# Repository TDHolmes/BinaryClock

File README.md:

# Binary Clock
A simple clock that displays the time in [binary coded decimal][BCD wiki link].

## PCB

![alt text][PCB picture]

The current design uses an Atmel [ATtiny4313][attiny link] microcontroller in conjunction with a Maxim [DS3231M][ds3231m link] [RTC][RTC wiki link] for accurate time keeping. The LEDs are driven with a [STP16CPC26][stp16cpc26 link] constant current LED driver along with [high-side MOSFETs][mosfet wiki link] for [multiplexing][multiplexing wiki link].

## LED Driving Scheme

The LEDs are driven by multiplexing the rows and columns. The columns are dirven individually via PMOS transistors. The rows are daisy chained and driven by the [STP16CPC26][stp16cpc26 link]. The columns are refreshed at an effective rate of 360 Hz to be equivallent to 60 Hz refresh rate.

In order to get more than basic red, green and blue combinations, the LEDs have four time slots to create more color combinations. So in reality, the LEDs are updated at (60 Hz) * (6 columns) * (4 bit color) = 1440 Hz.

Below shows the connectivity of the LEDs to the driver chips.

![alt text][Multiplex - off]

Below is a snapshot in time when the minute ones column is active.

![alt text][Multiplex - on]

And below is a gif of multiplexing in action.

![alt text][GIF]

## GUI
The user interface communicates to the PCB via a [UART][UART wiki link] through a USB to serial converter chip. The user interface can do a few things:
- set the time to the current computer system time
- set a custom time
- set one or all LEDs to a certain color
- clear one or all LEDs

![alt text][GUI picture]

[BCD wiki link]: https://en.wikipedia.org/wiki/Binary-coded_decimal
[attiny link]: https://www.atmel.com/devices/ATTINY4313.aspx
[ds3231m link]: https://www.maximintegrated.com/en/products/digital/real-time-clocks/DS3231M.html
[stp16cpc26 link]: https://www.st.com/content/st_com/en/products/power-management/led-drivers/led-array-drivers/stp16cpc26.html
[Multiplex - off]: https://raw.githubusercontent.com/TDHolmes/BinaryClock/master/documents/pictures/binaryClock_multiplexLogic_notOn.png "Diagram of the connections if the LEDs"
[Multiplex - on]: https://raw.githubusercontent.com/TDHolmes/BinaryClock/master/documents/pictures/binaryClock_multiplexLogic_on.png "Diagram of a snapshot when the minute ones column is active."
[GIF]: https://raw.githubusercontent.com/TDHolmes/BinaryClock/master/documents/pictures/binary_clock_demo.gif "GIF of the multiplexing"
[PCB picture]: https://raw.githubusercontent.com/TDHolmes/BinaryClock/master/documents/pictures/BinaryClock_rev1.JPG "Binary Clock v1 displaying 20:31:08 (8:31 PM)"
[RTC wiki link]: https://en.wikipedia.org/wiki/Real-time_clock
[mosfet wiki link]: https://en.wikipedia.org/wiki/MOSFET#Single-type
[multiplexing wiki link]: https://en.wikipedia.org/wiki/Multiplexing
[GUI picture]: https://raw.githubusercontent.com/TDHolmes/BinaryClock/master/documents/pictures/BinaryClockGUI.png "Binary Clock GUI v1.0"
[UART wiki link]: https://en.wikipedia.org/wiki/Universal_asynchronous_receiver/transmitter

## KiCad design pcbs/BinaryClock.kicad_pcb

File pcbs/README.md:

# Binary-Clock-v2.0
Board and schematic for the binary clock project.

<br />This work is licensed under a <a rel="license" href="http://creativecommons.org/licenses/by-nc-sa/4.0/">Creative Commons Attribution-NonCommercial-ShareAlike 4.0 International License</a>.

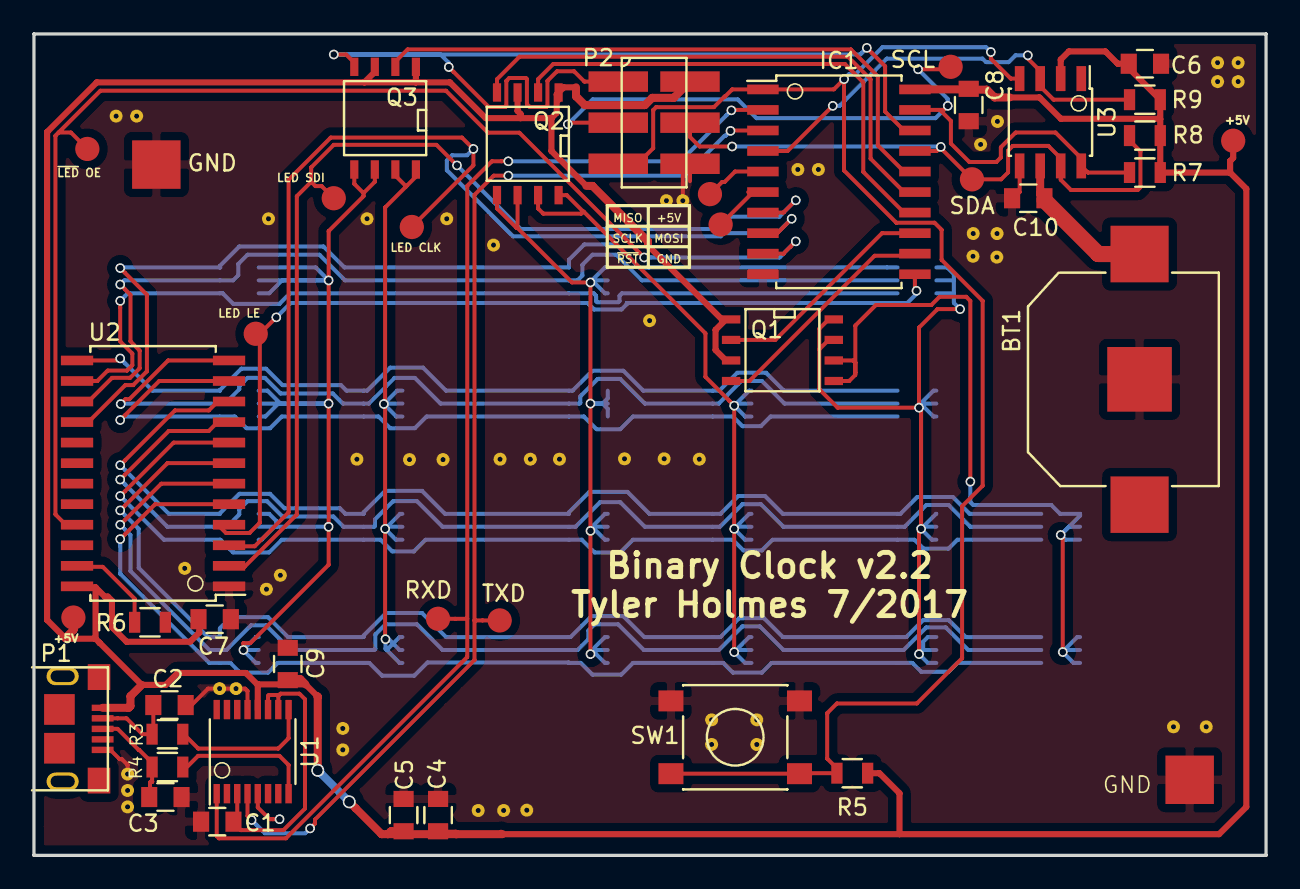
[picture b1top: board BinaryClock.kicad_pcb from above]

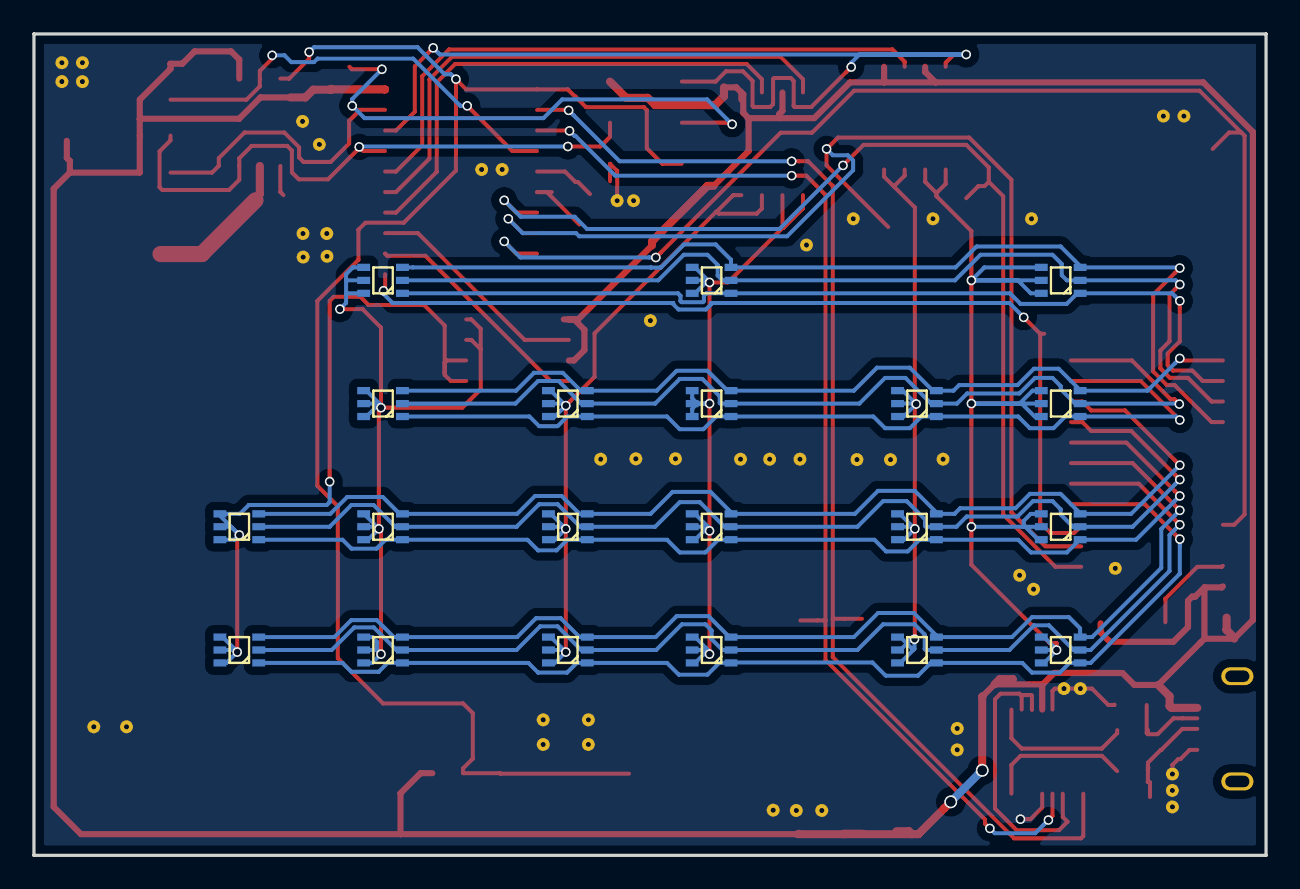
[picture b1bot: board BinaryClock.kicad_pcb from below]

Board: 2 copper layers, 76.2 x 50.8 mm, 62 parts (20 on the bottom side), 45 nets.

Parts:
BT1: CR1220; S8201-46R
C1: .1 uF; C_0805
C2, C3: 47 pF; C_0805
C4: 1 uF; C_0805
C5: 4.7 uF; C_0805
C6, C7, C8, C9, C10: 0.1 uF; C_0805
D_H_1, D_H_2, D_H_4, D_H_8, D_H_10, D_H_20: CLY6D-FKC; CREELED_6
D_M_1, D_M_2, D_M_4, D_M_8, D_M_10, D_M_20, D_M_40: CLY6D-FKC; CREELED_6
D_S_1, D_S_2, D_S_4, D_S_8, D_S_10, D_S_20, D_S_40: CLY6D-FKC; CREELED_6
IC1: ATTINY2313A-S; SOIC-20_7.5x12.8mm_Pitch1.27mm
P1: USB_OTG; 2013499-1
P2: CONN_02X03; 2x3_header_smd_0.1in
Q1, Q2, Q3: DMG9933USD; SOIC-8-N
R3, R4: R27; R_0805
R5, R7, R8, R9: 1K; R_0805
R6: 2K; R_0805
SW1: SW_PUSH; SW_SPST_PTS645
U1: FT230XS; SSOP-16_3.9x4.9mm_Pitch0.635mm
U2: STP16CPC26; SOIC-24_7.5x15.4mm_Pitch1.27mm
U3: DS3231M; SOIC-8_3.9x4.9mm_Pitch1.27mm
W1, W2, W5, W6, W7, W8, W9, W10, W11, W12, W13, W14: TEST_1P; Measurement_Point_Round-SMD-Pad_Small
W3, W4: TEST_1P; Measurement_Point_Square-SMD-Pad_Big

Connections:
+5V: C4.1, C5.1, C6.1, C7.1, C8.1, C9.1, IC1.20, P1.1, P2.2, Q1.1, Q1.3, Q2.1, Q2.3, Q3.1, Q3.3, R5.1, R7.1, R8.1, R9.1, U1.12, U2.24, U3.2, W1.1, W2.1
+BATT: BT1.1, C10.1, U3.6
/LED_Sheet/BLU_EIG_CAT: D_H_8.1, D_M_8.1, D_S_8.1, U2.14
/LED_Sheet/BLU_FOU_CAT: D_H_4.1, D_M_4.1, D_M_40.1, D_S_4.1, D_S_40.1, U2.11
/LED_Sheet/BLU_ONE_CAT: D_H_1.1, D_H_10.1, D_M_1.1, D_M_10.1, D_S_1.1, D_S_10.1, U2.5
/LED_Sheet/BLU_TWO_CAT: D_H_2.1, D_H_20.1, D_M_2.1, D_M_20.1, D_S_2.1, D_S_20.1, U2.8
/LED_Sheet/GRE_EIG_CAT: D_H_8.2, D_M_8.2, D_S_8.2, U2.15
/LED_Sheet/GRE_FOU_CAT: D_H_4.2, D_M_4.2, D_M_40.2, D_S_4.2, D_S_40.2, U2.12
/LED_Sheet/GRE_ONE_CAT: D_H_1.2, D_H_10.2, D_M_1.2, D_M_10.2, D_S_1.2, D_S_10.2, U2.6
/LED_Sheet/GRE_TWO_CAT: D_H_2.2, D_H_20.2, D_M_2.2, D_M_20.2, D_S_2.2, D_S_20.2, U2.9
/LED_Sheet/RED_EIG_CAT: D_H_8.3, D_M_8.3, D_S_8.3, U2.16
/LED_Sheet/RED_FOU_CAT: D_H_4.3, D_M_4.3, D_M_40.3, D_S_4.3, D_S_40.3, U2.13
/LED_Sheet/RED_ONE_CAT: D_H_1.3, D_H_10.3, D_M_1.3, D_M_10.3, D_S_1.3, D_S_10.3, U2.7
/LED_Sheet/RED_TWO_CAT: D_H_2.3, D_H_20.3, D_M_2.3, D_M_20.3, D_S_2.3, D_S_20.3, U2.10
GND: BT1.2, C1.2, C2.2, C3.2, C4.2, C5.2, C6.2, C7.2, C8.2, C9.2, C10.2, IC1.10, P1.5, P2.6, R6.2, SW1.1, U1.5, U1.13, U2.1, U3.5, W3.1, W4.1
HOU_ONE_ANO: IC1.13, Q1.2
HOU_TEN_ANO: IC1.12, Q1.4
LEDDRV_CLK: IC1.8, U2.3, W8.1
LEDDRV_LE: IC1.11, U2.4, W5.1
LEDDRV_SDI: IC1.7, U2.2, W7.1
MIN_ONE_ANO: IC1.15, Q2.4
MIN_TEN_ANO: IC1.14, Q2.2
unnamed: C1.1, U1.3, U1.10, U1.11
unnamed: C2.1, P1.2, R3.1
unnamed: C3.1, P1.3, R4.1
unnamed: D_H_1.4, D_H_1.5, D_H_1.6, D_H_2.4, D_H_2.5, D_H_2.6, D_H_4.4, D_H_4.5, D_H_4.6, D_H_8.4, D_H_8.5, D_H_8.6, Q1.7, Q1.8
unnamed: D_H_10.4, D_H_10.5, D_H_10.6, D_H_20.4, D_H_20.5, D_H_20.6, Q1.5, Q1.6
unnamed: D_M_1.4, D_M_1.5, D_M_1.6, D_M_2.4, D_M_2.5, D_M_2.6, D_M_4.4, D_M_4.5, D_M_4.6, D_M_8.4, D_M_8.5, D_M_8.6, Q2.5, Q2.6
unnamed: D_M_10.4, D_M_10.5, D_M_10.6, D_M_20.4, D_M_20.5, D_M_20.6, D_M_40.4, D_M_40.5, D_M_40.6, Q2.7, Q2.8
unnamed: D_S_1.4, D_S_1.5, D_S_1.6, D_S_2.4, D_S_2.5, D_S_2.6, D_S_4.4, D_S_4.5, D_S_4.6, D_S_8.4, D_S_8.5, D_S_8.6, Q3.5, Q3.6
unnamed: D_S_10.4, D_S_10.5, D_S_10.6, D_S_20.4, D_S_20.5, D_S_20.6, D_S_40.4, D_S_40.5, D_S_40.6, Q3.7, Q3.8
unnamed: IC1.5, W13.1
unnamed: IC1.6, W14.1
unnamed: R3.2, U1.9
unnamed: R4.2, U1.8
unnamed: R6.1, U2.23
RTC_SCL: IC1.19, P2.3, R7.2, U3.8, W9.1
RTC_SDA: IC1.17, P2.4, R8.2, U3.7, W10.1
RTC_SQW: IC1.4, R9.2, U3.3
SEC_ONE_ANO: IC1.18, P2.1, Q3.4
SEC_TEN_ANO: IC1.16, Q3.2
UART_RXD: IC1.2, U1.1, W11.1
UART_TXD: IC1.3, U1.4, W12.1
~LEDDRV_OE: IC1.9, U2.21, W6.1
~RST: IC1.1, P2.5, R5.2, SW1.2, U3.4

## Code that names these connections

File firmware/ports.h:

#ifndef PORTS_H__
#define PORTS_H__

#include <avr/io.h>

/*! \file ports.h
    \brief Defines what pins are connected to and defines useful macros for setting certain
    pins.
*/

//! PORT A PIN DEFINITIONS
#define IND_LED0     PA0
#define RTC_SQW      PA1
// Pin PA2 is reset input

//! PORT B PIN DEFINITIONS
#define HOUR_TEN_ANO PB0
#define HOUR_ONE_ANO PB1
#define MIN_TEN_ANO  PB2
#define MIN_ONE_ANO  PB3
#define SEC_TEN_ANO  PB4
#define RTC_SDA      PB5
#define SEC_ONE_ANO  PB6
#define RTC_SCL      PB7

//! PORT D PIN DEFINITIONS
#define UART_RXD    PD0
#define UART_TXD    PD1
#define IND_LED1    PD2
#define LEDDRV_SDI  PD3
#define LEDDRV_CLK  PD4
#define LEDDRV_OE   PD5
#define LEDDRV_LE   PD6
// no 7th pin on the port

#define ANO_PORT PORTB  //!< The annode of the LEDs is on port B

//! Macro to set the LED Driver output enable pin to either high or low
#define LEDDRV_OE_SET(val)  (val ? PORTD |= (1 << LEDDRV_OE) : (PORTD &= ~(1 << LEDDRV_OE)))
//! Macro to set the LED Driver latch enable pin to either high or low
#define LEDDRV_LE_SET(val)  (val ? PORTD |= (1 << LEDDRV_LE) : (PORTD &= ~(1 << LEDDRV_LE)))
//! Macro to set the LED Driver serial data in pin to either high or low
#define LEDDRV_SDI_SET(val) (val ? PORTD |= (1 << LEDDRV_SDI) : (PORTD &= ~(1 << LEDDRV_SDI)))
//! Macro to set the LED Driver clock pin to either high or low
#define LEDDRV_CLK_SET(val) (val ? PORTD |= (1 << LEDDRV_CLK) : (PORTD &= ~(1 << LEDDRV_CLK)))

//! Macro to set the debug LED 0 pin to either high or low
#define LED0_set(val) (val ? (PORTA |= 1 << IND_LED0) : (PORTA &= ~(1 << IND_LED0)))
//! Macro to set the debug LED 1 pin to either high or low
#define LED1_set(val) (val ? (PORTD |= 1 << IND_LED1) : (PORTD &= ~(1 << IND_LED1)))
//! Macro to toggle the debug LED 0 pin
#define LED0_toggle() (PORTA ^= (1 << IND_LED0))
//! Macro to toggle the debug LED 1 pin
#define LED1_toggle() (PORTD ^= (1 << IND_LED1))

#endif /* PORTS_H__ */

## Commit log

2016-07-08 initial add of files
2016-07-26 Added many new files
    Added a UART driver, UART functionality, a general purpose ring buffer,
    and some minor other changes
2016-07-27 Updated makefile to add fuse bit descriptions
2016-07-30 Many changes....
2016-07-30 Added ifndef guards to headers
2016-07-31 A lot of structural changes
    Rethought many structural things. Thoughts in plan_of_attack.txt. Will
    most likely change most of the LED and LED driver code
2016-07-31 Roughing out new LED functionality
2016-07-31 Changed naming scheme 'LEDs' to 'LED'
    brings more unification to naming across files
2016-08-01 Continued restructuring and added an API to send commands
2016-08-04 Major overhaul of the LED driver section.
    The change is mostly done in this implementation and is compiling. No
    testing yet.
2016-08-04 changed hierarchy
2016-08-05 added gitignore
2016-08-05 many changes
2016-08-05 added i2c functionality and some compiled binaries
2016-08-05 changed the gitignore file and removed object files.
2016-08-08 developing i2c & rtc library
2016-08-12 added many things
    I should break this commit up into multiple….
2016-08-12 committing changes before doing dangerous macro to add docstrings
2016-08-12 Added custom docstrings
2016-08-13 i2c and etc development
2016-08-14 Updates to many files, added a test project to verify the LED driver
2016-08-22 Many things
    - changed to retval_t and bool_t types
    - made UART work
2016-08-22 many changes as usual
    - UART added functionality
    - I2C almost works
    - changed I2C to bit bang, will most likely switch to an ifdef for bit
    bang mode vs. USI mode
2016-08-22 Update i2c.c
    Change read write mask logic
2016-08-23 Added a bitang ifdef in the i2c driver
2016-08-23 fleshed out i2c bitbang & deleted ringbuffertest project
2016-08-23 I2C Improvements
    Write seems to be working 100%
    Read isn’t. It isn’t seeing NACKs and isn’t writing the address to be
    read from it seems
2016-08-24 working with RTC interrupt
    Prototype working with RTC (read / write with 1 hz interrupt for time
    keeping)
2016-08-26 added UART receive length detection & refactored main to accept UART commands
2016-08-27 Fully working!
    As of this commit, the project is fully up and running.
2016-08-28 Added a GUI and made minor firmware changes
2016-08-28 fixed port issue
    Does not crash if no com device plugged in. Now refreshes list on click
    of the dropdown menu
    Also made Mac return usbserial ports without checking if you can
    connect. (much faster)
2016-08-29 UART commands now check for start byte
    in order to avoid getting out of sync until powercycle, we start with 0xAA in all commands. Still need to change python API to reflect these changes
2016-08-30 many things...
    -get rid of tracking multiplexer count
    -switch order of clearing multiplexer count and rtc count to avoid
    falsely clearing it
    -add start_byte_received reset to FALSE after processing a command
2016-09-03 Adding in PCB files
2016-09-03 added picture of the GUI
2016-09-03 fixed image
2016-09-03 created a readme
2016-09-06 Added diagrams to explain multiplexing
2016-09-06 Added signals
2016-09-06 Updated documentation.
    Added documentation to describe the multiplexing scheme.
2016-09-06 Added picture of the clock runnning
2016-09-06 Added picture of clock running to documentation
2016-09-11 Create gh-pages branch via GitHub
2016-09-11 Added oxygen documentation
2016-09-11 added link to doxygen documentation
2016-09-11 Fixing link to doxygen documentation
2016-09-11 changing doxygen link to go to index.html
2016-09-11 trying to get the link to doxygen docs to work
2016-09-11 trying to fix the gh-pages branch
2016-09-11 trying to fix the link to doxygen docs
2016-09-11 making doxygen link relative
2016-09-11 Formatting changes
2016-09-11 updated documentation
2016-09-12 added software documentation
2016-09-12 added in software documentation
2016-09-12 moving the nojekyl file
2016-09-15 Added gif example
2016-09-15 added gif demo
2016-09-15 Added gif demo of multiplexing
2016-09-15 Added gif demo of multiplexing on web page
2016-09-20 Changed to 9600 baud and changed how we set the baud rate
2016-09-25 Fixed routing issues, fixed paste layer issues, and eliminated electrolytic caps
2016-09-26 Added a UART_peak_byte function & ring_buffer_peak_data function
2016-09-26 Deleted the not-needed silkscreen on the LEDs side of the PCB
2016-09-30 Adding the positioning files for automated assembly
2016-10-08 Changed led_color_t to LED_color_t
2016-10-08 Regenerated documents
2016-10-16 Refactored based on the UART start byte and what it returns
2016-10-17 refactored to decrease size and added some functionality to check if the RTC oscillator stopped when in battery backup mode.
2016-10-24 Saving clock color and fixing the GUI
2017-06-11 Create CNAME
2017-06-11 Update CNAME
2017-06-11 removing .DS_Store files
2017-06-11 removing documentation from the main branch
2017-06-11 readability changes
2017-06-11 removing software html from main branch
2017-06-11 making documentation building relative and adding a script to do it
2017-06-11 minor changes to build script and added a bash script to update gh-pages branch
2017-06-11 removing unused files
2017-06-11 fixing some path things
2017-06-11 fixing folder names
2017-06-11 removing ds store file
2017-06-11 adding realpath protection around __file__
2017-06-11 updating paths
2017-06-11 more verbose output of what's going on
2017-06-11 temp copy out
2017-06-11 stupid recursive copy
2017-06-11 removing temp copy
2017-06-11 stupid. recursive. crap.
2017-06-11 adding temp read
2017-06-11 adding temp read for wait
2017-06-11 updating docs and adding more .gitignore folder paths
2017-06-11 adding checks for successful returncodes
2017-06-11 removing /dev/null redirects
2017-06-11 removing unnecessary check
2017-06-11 switching back to using jekyll
2017-06-11 minor change to check jekkyl is working
2017-06-11 Set theme jekyll-theme-minimal and migrate Page Generator content
2017-06-11 Switching back to the minimal theme
2017-06-11 adding GIF back in
2017-06-11 adding change to index md file
2017-06-12 adding http redirect
2017-06-20 adding a favicon
2017-06-20 adding favicon code to html
2017-06-20 making some minor formatting changes
2017-06-20 removing the backup version
2017-06-20 minor changes for 2.2 release
2017-12-22 fixin gitignore and cleanup
2017-12-22 some more cleanup and hide silk on LED side of PCB
2018-02-06 fixes to scripts
2018-02-06 adding comment about fuse byte
2018-10-29 non functional whitespace changes
2018-10-29 most recent elf/hex
2018-10-29 v2 schematic
2019-11-09 updated pictures
2019-11-09 crop
2019-11-09 update README too
2020-06-12 remove http redirect
2020-06-12 some http -> https
2022-08-29 py2/py3 compatibility
